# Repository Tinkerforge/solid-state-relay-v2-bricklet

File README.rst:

Solid State Relay Bricklet 2.0
==============================

This repository contains the firmware source code and the hardware design
files. The documentation generator configs can be found at
https://github.com/Tinkerforge/generators

Repository Content
------------------

software/:
 * examples/: Examples for all supported languages
 * build/: Compiled files
 * src/: Source code of firmware
 * Makefile: Makefile to build project

hardware/:
 * Contains KiCad project files and additionally schematics as PDF

datasheets/:
 * Contains datasheets for sensors and complex ICs that are used

Hardware
--------

The hardware is designed with the open source EDA Suite KiCad
(http://www.kicad.org). Before you are able to open the files,
you have to install the Tinkerforge kicad-libraries
(https://github.com/Tinkerforge/kicad-libraries). You can either clone
them directly in hardware/ or clone them in a separate folder and
symlink them into hardware/
(ln -s kicad_path/kicad-libraries project_path/hardware). After that you
can open the .pro file in hardware/ with KiCad and from there view and
modify the schematics and the PCB layout.

Software
--------

If you want to do your own Brick/Bricklet firmware development we highly
recommend that you use our build environment setup script and read the
tutorial (https://www.tinkerforge.com/en/doc/Tutorials/Tutorial_Build_Environment/Tutorial.html).

To compile the C code we recommend you to install the newest GNU Arm Embedded
Toolchain (https://launchpad.net/gcc-arm-embedded/+download).
You also need to install bricklib2 (https://github.com/Tinkerforge/bricklib2).

You can either clone it directly in software/src/ or clone it in a
separate folder and symlink it into software/src/
(ln -s bricklib_path/bricklib2 project_path/software/src/). Finally make sure to
have CMake installed (http://www.cmake.org/cmake/resources/software.html).

After that you can build the firmware by invoking make in software/.
The firmware (.zbin) can then be found in software/build/ and uploaded
with brickv (click button "Flashing" on start screen).

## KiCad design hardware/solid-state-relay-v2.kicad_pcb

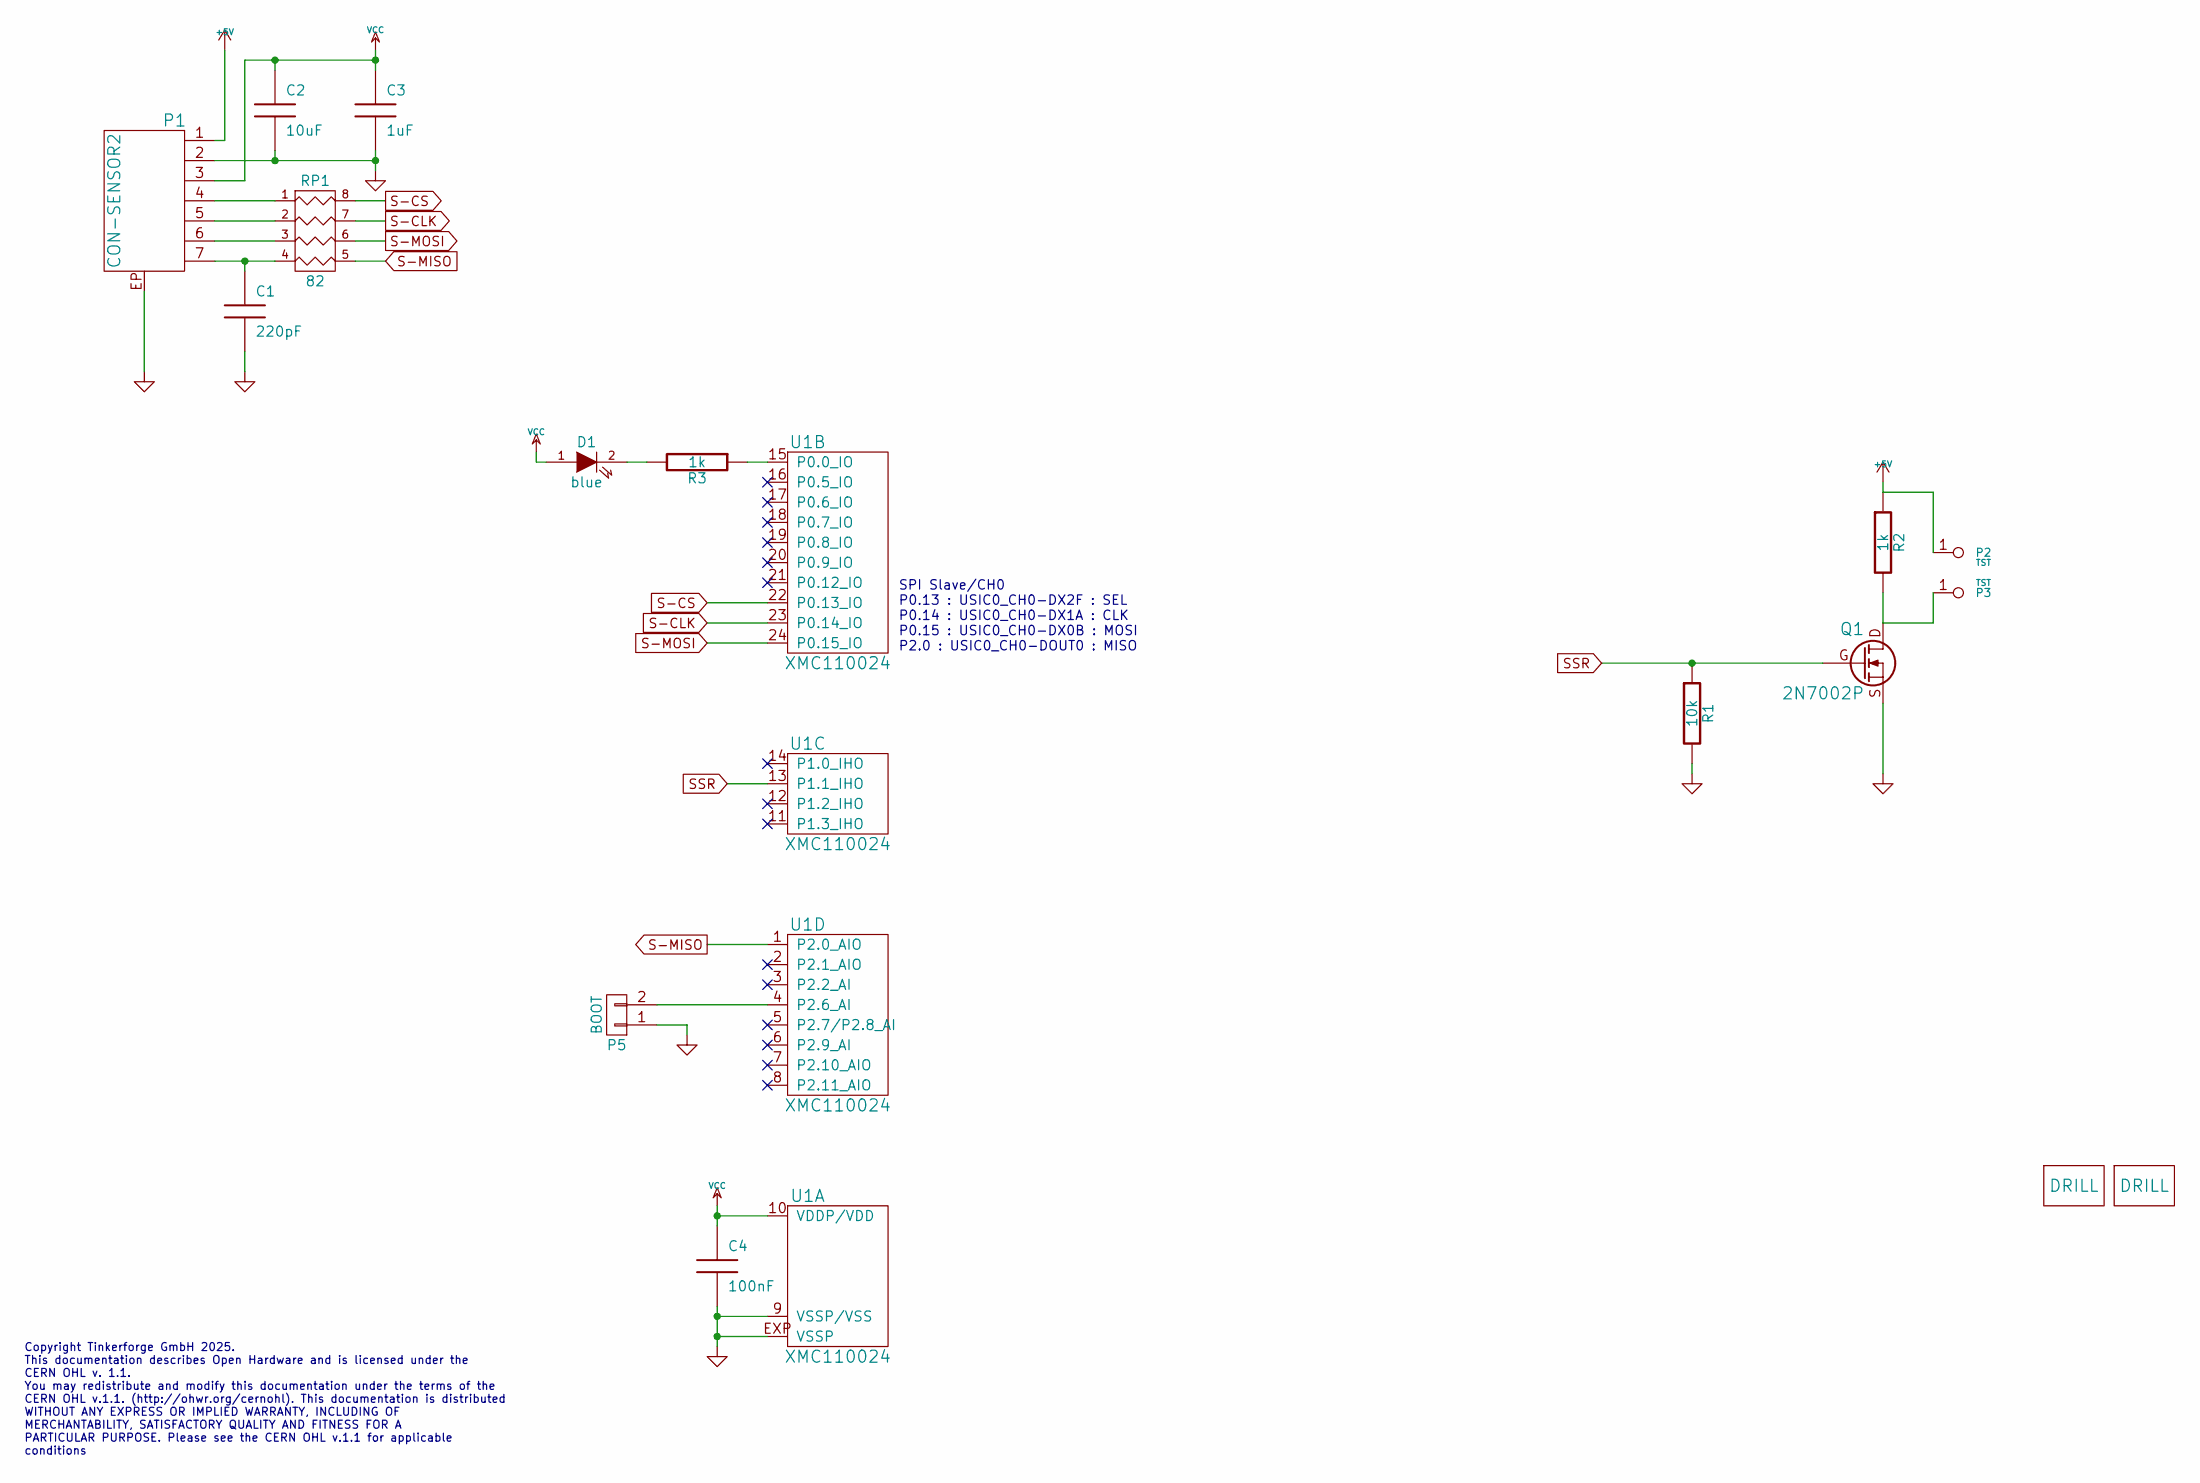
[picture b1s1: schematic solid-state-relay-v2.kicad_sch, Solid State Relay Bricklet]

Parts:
C1: 220pF; C0402F
C2: 10uF; C0805
C3: 1uF; C0603F
C4: 100nF; C0603F
D1: blue; D0603F
P1: CON-SENSOR2
P2, P3: TST; Drill
P5: BOOT; SolderJumper
Q1: 2N7002P; SOT23GDS
R1: 10k; R0603F
R2, R3: 1k; R0603F
RP1: 82; 4X0402
U1: XMC110024; QFN24-4x4mm-0.5mm
U2, U3: DRILL; DRILL_NP

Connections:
+5V: P1.1, P2.1, R2.1
GND: C1.2, C2.2, C3.2, C4.2, P1.2, P1.EP, P5.1, Q1.S, R1.2, U1.9 (VSSP/VSS), U1.EXP (VSSP)
unnamed: C1.1, P1.7, RP1.4
unnamed: D1.2 (K), R3.2
unnamed: P1.4, RP1.1
unnamed: P1.5, RP1.2
unnamed: P1.6, RP1.3
unnamed: P5.2, U1.4 (P2.6_AI)
unnamed: P3.1, Q1.D, R2.2
unnamed: R3.1, U1.15 (P0.0_IO)
S-CLK: RP1.7 (R2), U1.23 (P0.14_IO)
S-CS: RP1.8 (R1), U1.22 (P0.13_IO)
S-MISO: RP1.5 (R4), U1.1 (P2.0_AIO)
S-MOSI: RP1.6 (R3), U1.24 (P0.15_IO)
SSR: Q1.G, R1.1, U1.13 (P1.1_IHO)
VCC: C2.1, C3.1, C4.1, D1.1 (A), P1.3, U1.10 (VDDP/VDD)

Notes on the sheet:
SPI Slave/CH0 P0.13 : USIC0_CH0-DX2F : SEL P0.14 : USIC0_CH0-DX1A : CLK P0.15 : USIC0_CH0-DX0B : MOSI P2.0 : USIC0_CH0-DOUT0 : MISO
Copyright Tinkerforge GmbH 2025. This documentation describes Open Hardware and is licensed under the CERN OHL v. 1.1. You may redistribute and modify this documentation under the terms of the CERN OHL v.1.1. (http://ohwr.org/cernohl). This documentation is distributed WITHOUT ANY EXPRESS OR IMPLIE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

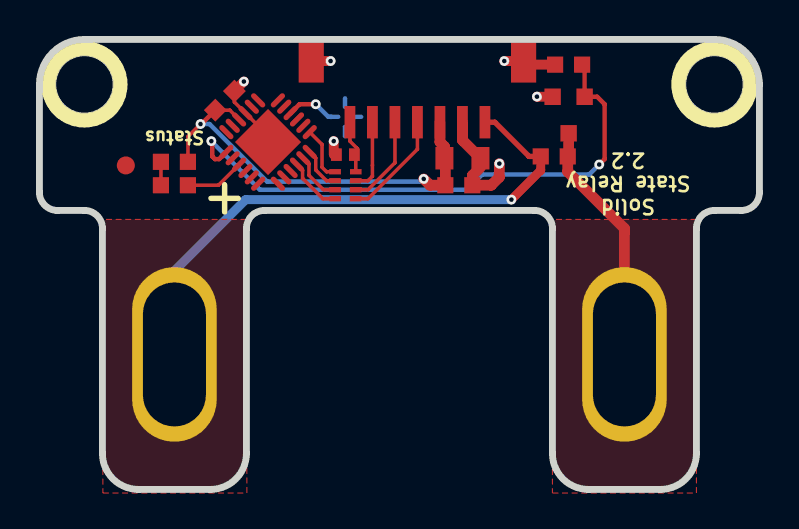
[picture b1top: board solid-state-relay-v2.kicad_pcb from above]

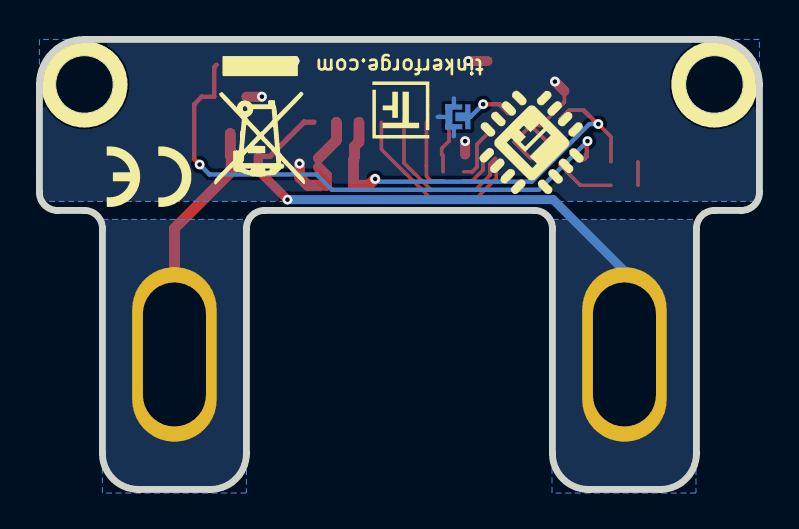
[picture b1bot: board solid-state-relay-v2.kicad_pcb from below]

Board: 2 copper layers, 40.0 x 25.0 mm, 20 parts (3 on the bottom side), 16 nets.

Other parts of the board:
Fiducial_Mark: VAL**; Fiducial_Mark
VAL: WEEE_7mm
VAL#2: CE_5mm

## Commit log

2017-09-18 Add datasheets
2017-09-18 Add schematic
2017-09-18 Fix footprints, optical adjustments
2017-09-18 Finished prototype
2017-09-18 Fix outlines
2017-09-18 Fix conductor paths
2017-10-13 Add initial stub implementation
2017-10-13 Add "status" marking for status LED
2017-10-19 fix outline edge cuts layer, fix weee logo
2017-10-23 Add 3d model (*.step & *.FCStd)
2017-10-26 change led position
2017-10-26 Implement relay set/get functionality
2017-10-26 Remove obsolete comments and debugging
2017-10-26 specify processor type
2017-12-07 Add examples
2018-01-26 c: Fine-tune define placement
2018-02-05 Update 3d model
2018-02-16 Add schematic (PDF)
2018-02-19 javascript: Close div tag correctly
2018-02-20 Cleanup KiCad libraries config
    Ensure LibDir=kicad-libraries and LibName1=tinkerforge.
    Remove special library.
2018-03-05 Remove unused flash-size define
2018-05-11 Rename files
2018-05-24 perl: Use strict in examples
2018-06-06 Add LabVIEW example
2018-06-18 Change capacitor footprint(s) to C0402F
2018-06-28 Fix readme
2018-07-11 Add Makefile with docker support
2018-07-11 Remove obsolete generate_makefile scripts
2018-07-11 Update directory structure and build instructions
2018-10-04 Increase version for new release (changes in bricklib2)
2018-10-04 Add rev to changelog
2018-11-06 Add rust examples
2018-11-07 rust: Accept host names for ip connection, fix naming inconsistencies
2018-12-14 Add go examples.
2018-12-18 go: Change import path.
2018-12-18 go: Change import path again.
2018-12-20 rust: Reformat examples.
2019-01-24 mqtt: Add examples.
2019-01-24 mqtt: Fix example header.
2019-01-24 mqtt: Remove executable bit in example permissions.
2019-01-24 go: Minor example fixes.
2019-01-24 mqtt: Minor example fixes.
2019-01-29 rust: Fix unused loop index.
2019-05-07 Make get-monoflop always return the current state to match documentation
2020-01-13 examples: Use python3 input instead of python2 raw_input.
2020-01-13 examples: mqtt: Remove trailing whitespace.
2020-03-16 Whitespace
2020-03-23 mqtt: Update for loop style
2020-04-07 examples: rust: Always block when calling bindings functions.
2020-08-19 Add uc examples.
2020-08-25 uc: Fix whitespace
2020-08-27 uc: Fix warnings.
2020-09-02 uc: Add example driver note.
2021-10-18 labview: Add special monoflop example
2021-10-25 Update KiCad link
    https://www.kicad.org/blog/2021/10/Avoid-links-to-former-kicad-domain/
2022-04-19 examples: uc: Rename TF_HalContext to TF_HAL.
2022-04-27 uc: Adapt to bindings changes
2022-07-06 Add license files.
2023-01-23 New standart layout. Switched to Kicad 6
2023-01-27 fix schematic library
2023-01-27 Hardware 2.1: Made Pcb bigger to fit on the 40mm grid. Data Cleanup
2025-05-20 version 2.2: add slotted holes
2025-10-04 Fix compatibility with new Docker build image (GCC 14.2.1)
2026-03-04 adapt outline to 5mm grid
2026-03-04 small dimensions changes
2026-03-04 fix layers

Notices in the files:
hardware/solid-state-relay-v2.kicad_pcb:
Licensed under CERN OHL v.1.1
Copyright (©) 2025, T.Schneidermann
hardware/solid-state-relay-v2.kicad_sch:
Copyright (©) 2023, T.Schneidermann
